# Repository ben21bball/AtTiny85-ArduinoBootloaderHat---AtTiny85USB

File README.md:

# AtTiny85-ArduinoBootloaderHat---AtTiny85USB
Want to set up an ATTiny85 as quickly as possible with a hot-swappable Arduino Uno R3 hat and USB adapter PCBs? Look no further!

This repository contains a project for an Arduino hat PCB for downloading a bootloader onto an ATtiny85 microcontroller and a PCB-based USB device for directly sending code to the ATtiny85. All PCB designs were intended to keep traces to one side of a PCB to enable the greatest number of tinkerers to recreate this to save them time with the ATtiny85 boot loading and programming. Hopefully this saves you time and money when making circuits to use the ATtiny85 with the Arduino IDE.

(This is for people who plan to make many ATTiny85-based devices and/or do not want their chip permanently soldered to an ugly USB board after programming.)

This is heavily inspired by the following links: https://circuitdigest.com/microcontroller-projects/attiny85-ic-programming-through-usb-using-digispark-bootloader https://circuitdiagrams.in/program-attiny85-microcontroller-using-usb/

Credit to the original tinkerers for coming up with these solutions or modifying them. I took issue with some of the diagrams in both of these links, as well as wanting to make a compact and open-source design. The circuit diagram for the USB device and the PCB layouts were designed in KiCAD. I will be adding a 3D printed enclosure for the USB device and the files will be added eventually.

https://resources.altium.com/p/how-design-custom-arduino-shield-board This is a link for the dimensions of a couple of Arduino boards, if you would like to design your own, this is where I started.

Arduino Hat

USB Board

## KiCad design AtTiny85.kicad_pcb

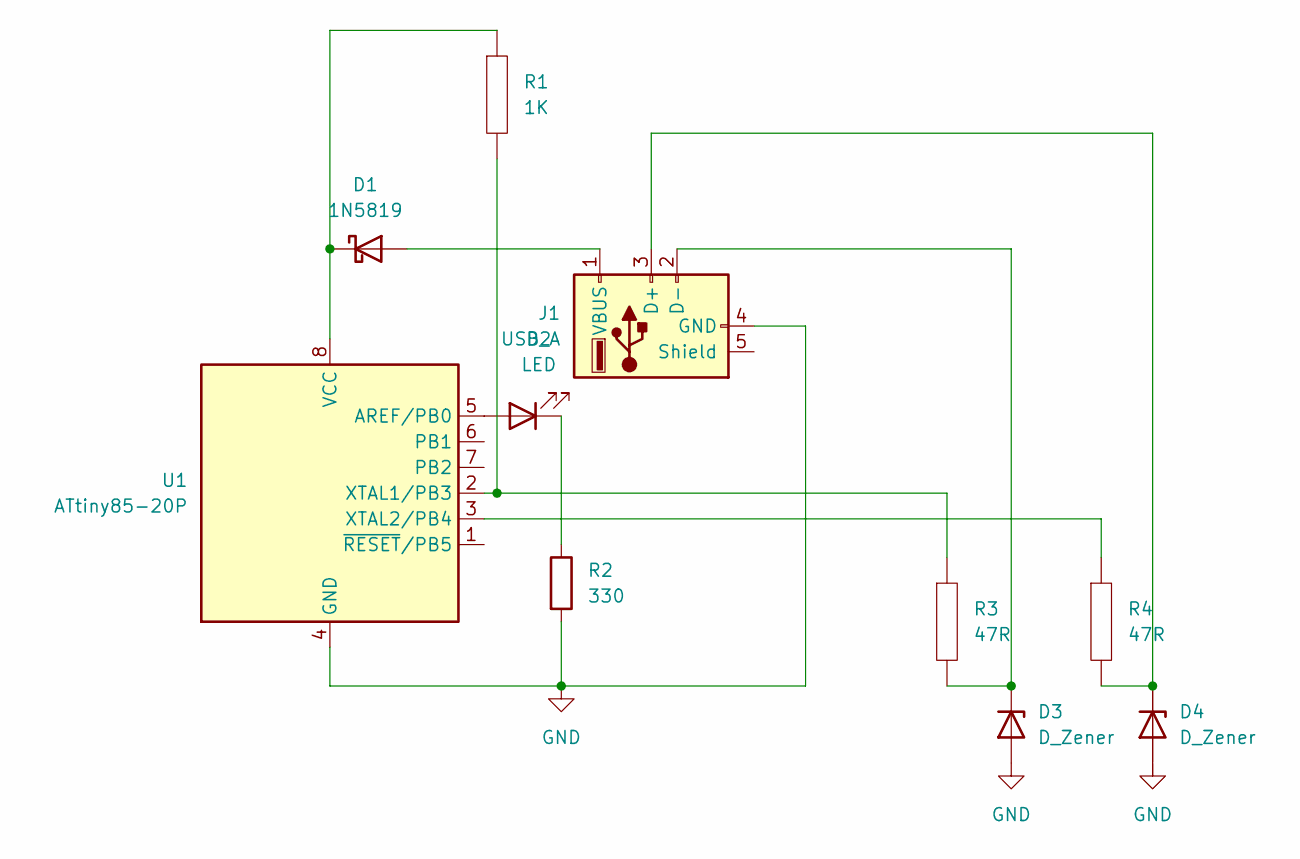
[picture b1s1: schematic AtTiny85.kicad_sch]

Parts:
D1: 1N5819; D_DO-41_SOD81_P10.16mm_Horizontal
D2: LED; LED_D3.0mm_Clear
D3, D4: D_Zener; D_A-405_P10.16mm_Horizontal
J1: USB_A; USB_A_CNCTech_1001-011-01101_Horizontal
R1: 1K; R_Axial_DIN0207_L6.3mm_D2.5mm_P10.16mm_Horizontal
R2: 330; R_Axial_DIN0207_L6.3mm_D2.5mm_P7.62mm_Horizontal
R3, R4: 47R; R_Axial_DIN0207_L6.3mm_D2.5mm_P7.62mm_Horizontal
U1: ATtiny85-20P; DIP-8_W7.62mm

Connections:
GND: D3.2 (A), D4.2 (A), J1.4 (GND), R2.2, U1.4 (GND)
unnamed: D2.1 (K), R2.1
unnamed: D2.2 (A), U1.5 (AREF/PB0)
unnamed: D3.1 (K), J1.2 (D-), R3.2
unnamed: D4.1 (K), J1.3 (D+), R4.2
unnamed: D1.2 (A), J1.1 (VBUS)
unnamed: D1.1 (K), R1.1, U1.8 (VCC)
unnamed: R1.2, R3.1, U1.2 (XTAL1/PB3)
unnamed: R4.1, U1.3 (XTAL2/PB4)

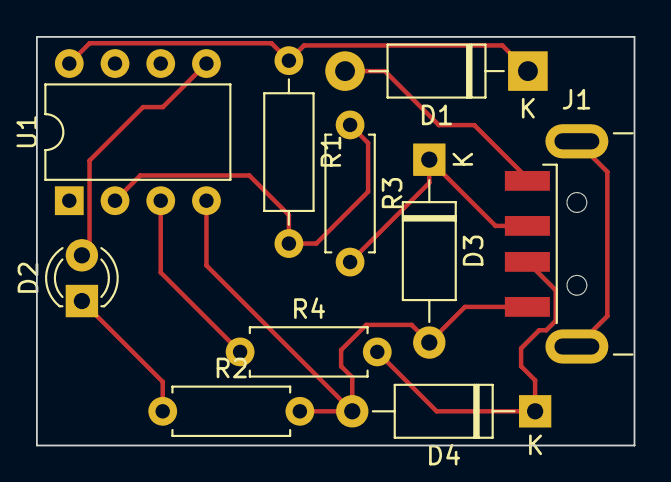
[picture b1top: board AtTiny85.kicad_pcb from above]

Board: 2 copper layers, 33.2 x 22.7 mm, 10 parts (0 on the bottom side), 9 nets.

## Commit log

2023-12-30 Add files via upload
    USB device KiCAD project files.
2023-12-30 Add files via upload
    Arduino Hat project files from KiCAD
